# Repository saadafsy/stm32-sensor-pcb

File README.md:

# STM32F411 Sensor Telemetry Board — Firmware

Bare-metal C (no HAL, direct CMSIS) + FreeRTOS firmware for a custom **4-layer** STM32F411RET6
sensor telemetry board. A BME280 environmental sensor and a 128×64 **SSD1306 OLED** share one
400 kHz I²C bus, arbitrated by a FreeRTOS mutex. Sensor readings are framed with a CRC-16/CCITT
protocol and streamed at 921600 baud over a CP2102N USB-UART bridge to a Python visualizer.

## Architecture — four FreeRTOS tasks
- **sensor_task** — reads + Bosch-compensates the BME280 over I²C, pushes samples to a queue
- **telemetry_task** — builds the CRC-framed binary packet and sends it under a UART mutex
- **display_task** — renders pages to the SSD1306; a **PA0/EXTI0 button** cycles pages via an ISR notification
- **heartbeat_task** — blinks the PA5 LED and kicks the IWDG watchdog

Shared I²C access is protected by an `i2c_mutex`; an `i2c_bus_recovery()` routine frees a wedged bus.

## Hardware (locked spec)
- MCU: **STM32F411RET6, LQFP-64** (LCSC C94355)
- PCB: **4-layer** — `F.Cu` signal / `In1.Cu` ground plane / `In2.Cu` +3V3 plane / `B.Cu` signal, 1.6 mm FR4
- BME280 @ I²C **0x77** (SDO→+3V3) · SSD1306 @ I²C **0x3C** · CP2102N USB-UART
- Clock: 8 MHz HSE → PLL → 100 MHz

## Layout
```
Core/Inc/   headers (clock, gpio, uart, i2c, bme280, crc, protocol, ssd1306, iwdg, FreeRTOSConfig)
Core/Src/   sources (+ main.c with the four tasks and the EXTI button ISR)
tools/      visualize.py — host-side telemetry viewer
hardware/   KiCad project (schematic, PCB, project)
docs/img/   board renders
```

## Build
Import into **STM32CubeIDE** as a bare-metal + FreeRTOS project for the STM32F411RET6
(develop on a NUCLEO-F411RE, deploy on the custom PCB). Flash over SWD/ST-Link.

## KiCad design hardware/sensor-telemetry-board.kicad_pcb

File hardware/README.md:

# Hardware

Custom 4-layer PCB designed in KiCad 9 (stackup: F.Cu / inner GND / inner +3V3 / B.Cu).

- `sensor-telemetry-board.kicad_pro` - project
- `sensor-telemetry-board.kicad_sch` - schematic
- `sensor-telemetry-board.kicad_pcb` - 4-layer layout

## Key parts

| Ref | Part | Role |
|-----|------|------|
| U1 | STM32F411CEU6 | MCU (Cortex-M4F, 100 MHz) |
| U? | BME280 | temperature / humidity / pressure over I2C |
| U? | CP2102N | USB-C to UART bridge |
| U? | AMS1117-3.3 | 3.3 V LDO |
| U? | USBLC6-2 | USB data-line ESD protection |
| Y1 | 8 MHz crystal | HSE reference for the 100 MHz PLL |

## Status

Design complete and DFM-validated (POFV across all vias); Gerbers, BOM, and CPL
can be regenerated from this project for a JLCPCB PCBA order. The board is in shipping 
and will be brought up soon (see the top-level README for status).

To export fabrication files: open the project in KiCad and run the Fabrication
Toolkit plugin, or export Gerbers / drill / BOM / CPL manually from the PCB and
schematic editors.

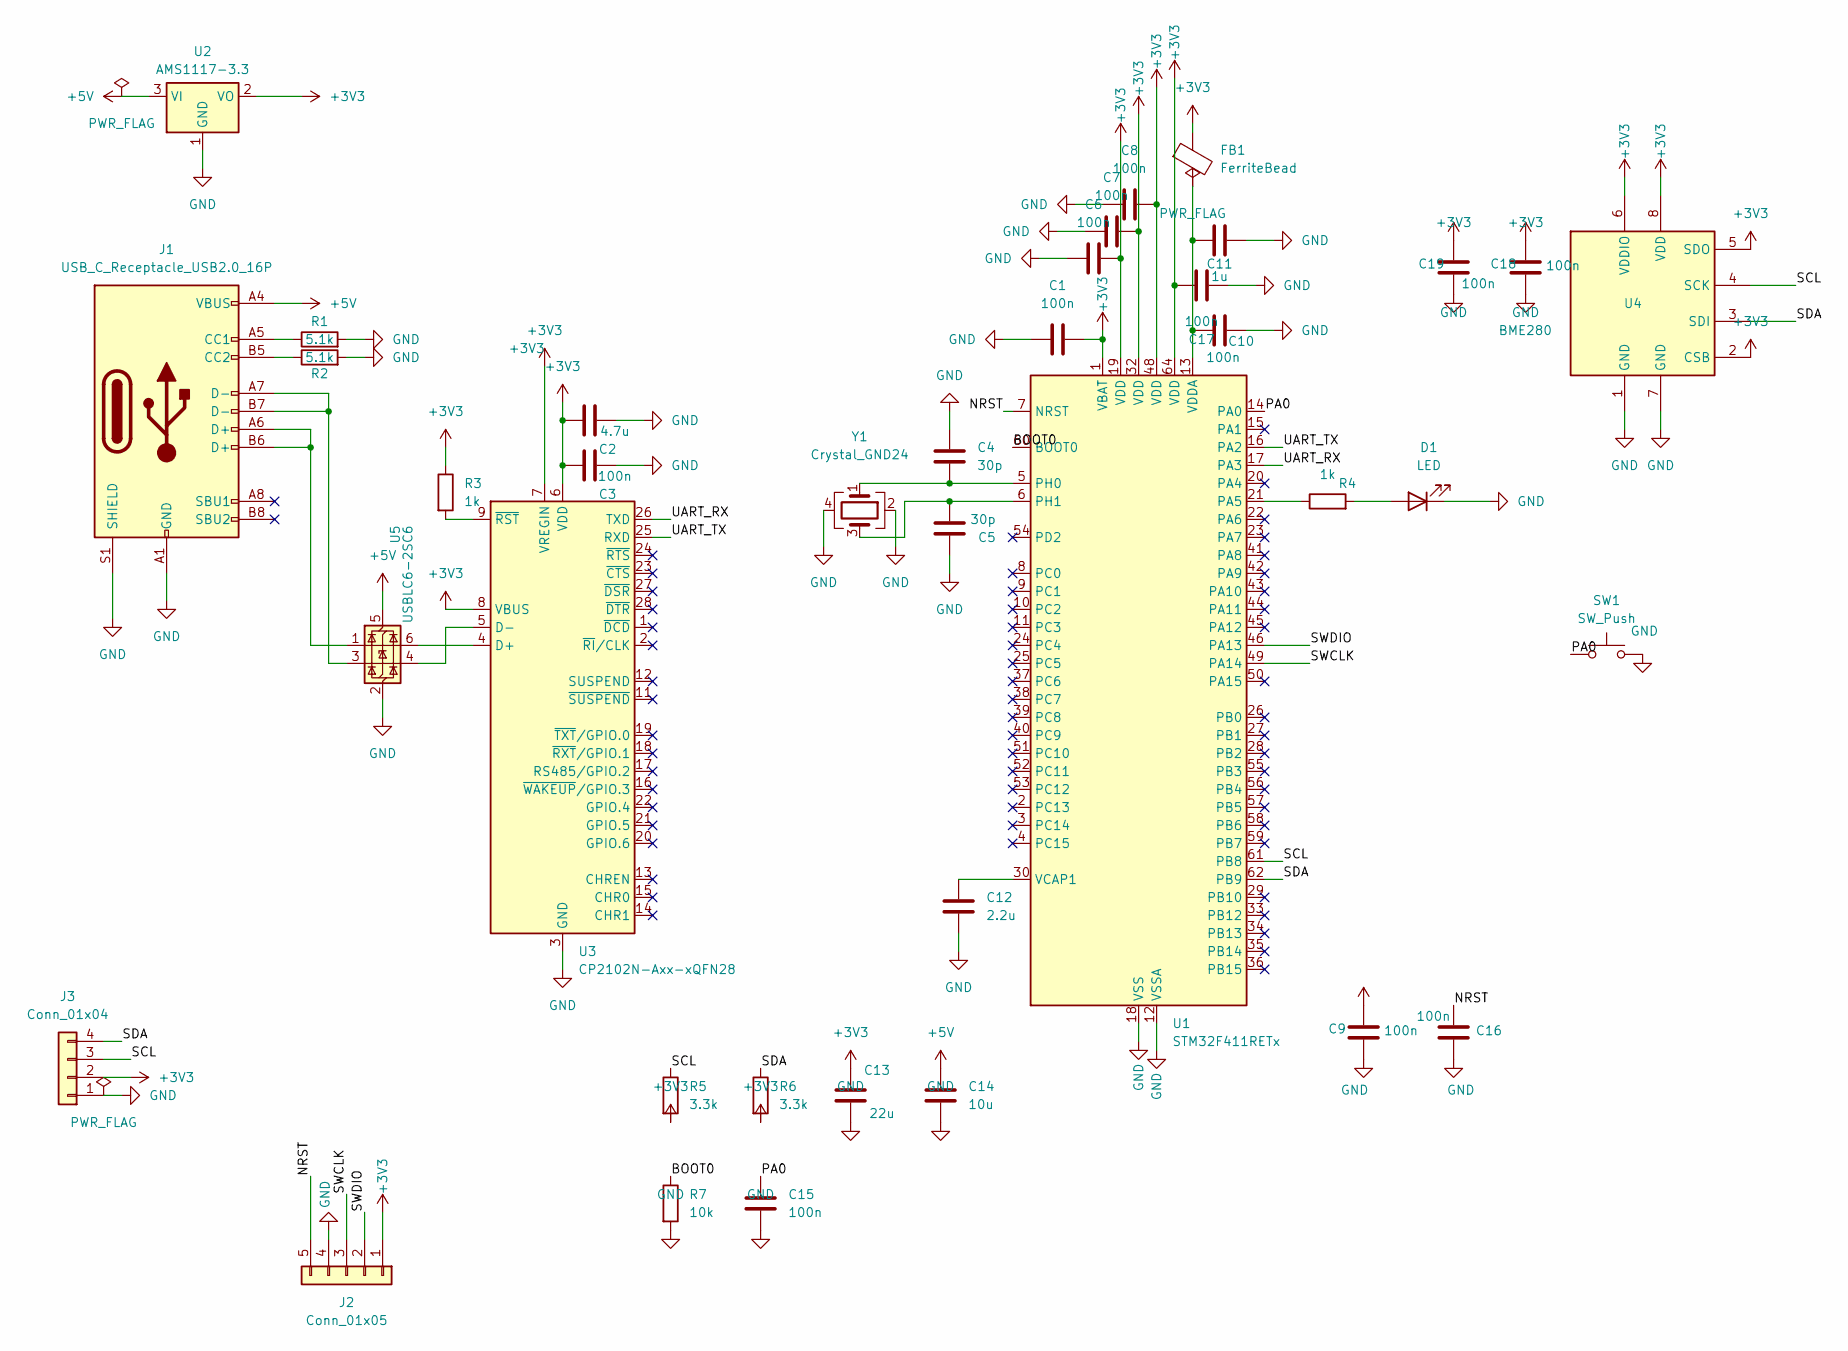
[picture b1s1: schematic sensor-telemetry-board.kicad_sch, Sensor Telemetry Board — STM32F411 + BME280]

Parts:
C1, C3, C6, C7, C8, C9, C10, C15, C16, C17, C18, C19: 100n; C_0402_1005Metric
C2: 4.7u; C_0603_1608Metric
C4, C5: 30p; C_0402_1005Metric
C11: 1u; C_0402_1005Metric
C12: 2.2u; C_0603_1608Metric
C13: 22u; C_0805_2012Metric
C14: 10u; C_0805_2012Metric
D1: LED; LED_0603_1608Metric
FB1: FerriteBead; L_0603_1608Metric
J1: USB_C_Receptacle_USB2.0_16P; USB_C_Receptacle_HRO_TYPE-C-31-M-12
J2: Conn_01x05; PinHeader_1x05_P2.54mm_Vertical
J3: Conn_01x04; PinHeader_1x04_P2.54mm_Vertical
R1, R2: 5.1k; R_0402_1005Metric
R3, R4: 1k; R_0402_1005Metric
R5, R6: 3.3k; R_0402_1005Metric
R7: 10k; R_0402_1005Metric
SW1: SW_Push; SW_SPST_PTS645Sx43SMTR92
U1: STM32F411RETx; LQFP-64_10x10mm_P0.5mm
U2: AMS1117-3.3; SOT-223-3_TabPin2
U3: CP2102N-Axx-xQFN28; QFN-28-1EP_5x5mm_P0.5mm_EP3.35x3.35mm
U4: BME280; Bosch_LGA-8_2.5x2.5mm_P0.65mm_ClockwisePinNumbering
U5: USBLC6-2SC6; SOT-23-6
Y1: Crystal_GND24; Crystal_SMD_3225-4Pin_3.2x2.5mm

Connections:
+3V3: C1.2, C2.2, C3.2, C6.2, C7.2, C8.2, C9.1, C13.1, C17.2, C18.1, C19.1, FB1.1, J2.1, J3.2, R3.1, R5.2, R6.2, U1.1 (VBAT), U1.19 (VDD), U1.32 (VDD), U1.48 (VDD), U1.64 (VDD), U2.2 (VO), U3.6 (VDD), U3.7 (VREGIN), U3.8 (VBUS), U4.2 (CSB), U4.5 (SDO), U4.6 (VDDIO), U4.8 (VDD)
+5V: C14.1, J1.A4 (VBUS), J1.A9 (VBUS), J1.B4 (VBUS), J1.B9 (VBUS), U2.3 (VI), U5.5 (VBUS)
/BOOT0: R7.1, U1.60 (BOOT0)
/NRST: C16.1, J2.5, U1.7 (NRST)
/PA0: C15.1, SW1.1, U1.14 (PA0)
/SCL: J3.3, R5.1, U1.61 (PB8), U4.4 (SCK)
/SDA: J3.4, R6.1, U1.62 (PB9), U4.3 (SDI)
/SWCLK: J2.3, U1.49 (PA14)
/SWDIO: J2.2, U1.46 (PA13)
/UART_RX: U1.17 (PA3), U3.26 (TXD)
/UART_TX: U1.16 (PA2), U3.25 (RXD)
GND: C1.1, C2.1, C3.1, C4.1, C5.1, C6.1, C7.1, C8.1, C9.2, C10.1, C11.1, C12.2, C13.2, C14.2, C15.2, C16.2, C17.1, C18.2, C19.2, D1.1 (K), J1.A1 (GND), J1.A12 (GND), J1.B1 (GND), J1.B12 (GND), J1.S1 (SHIELD), J2.4, J3.1, R1.2, R2.2, R7.2, SW1.2, U1.12 (VSSA), U1.18 (VSS), U1.31 (VSS), U1.47 (VSS), U1.63 (VSS), U2.1 (GND), U3.3 (GND), U3.29 (GND), U4.1 (GND), U4.7 (GND), U5.2 (GND), Y1.2, Y1.4
unnamed: D1.2 (A), R4.2
unnamed: J1.A5 (CC1), R1.1
unnamed: J1.B5 (CC2), R2.1
unnamed: J1.A6 (D+), J1.B6 (D+), U5.1 (I/O1)
unnamed: J1.A7 (D-), J1.B7 (D-), U5.3 (I/O2)
unnamed: R4.1, U1.21 (PA5)
unnamed: C4.2, U1.5 (PH0), Y1.1
unnamed: C5.2, U1.6 (PH1), Y1.3
unnamed: C12.1, U1.30 (VCAP1)
unnamed: C10.2, C11.2, FB1.2, U1.13 (VDDA)
unnamed: U3.4 (D+), U5.6 (I/O1)
unnamed: U3.5 (D-), U5.4 (I/O2)
unnamed: R3.2, U3.9 (~RST)

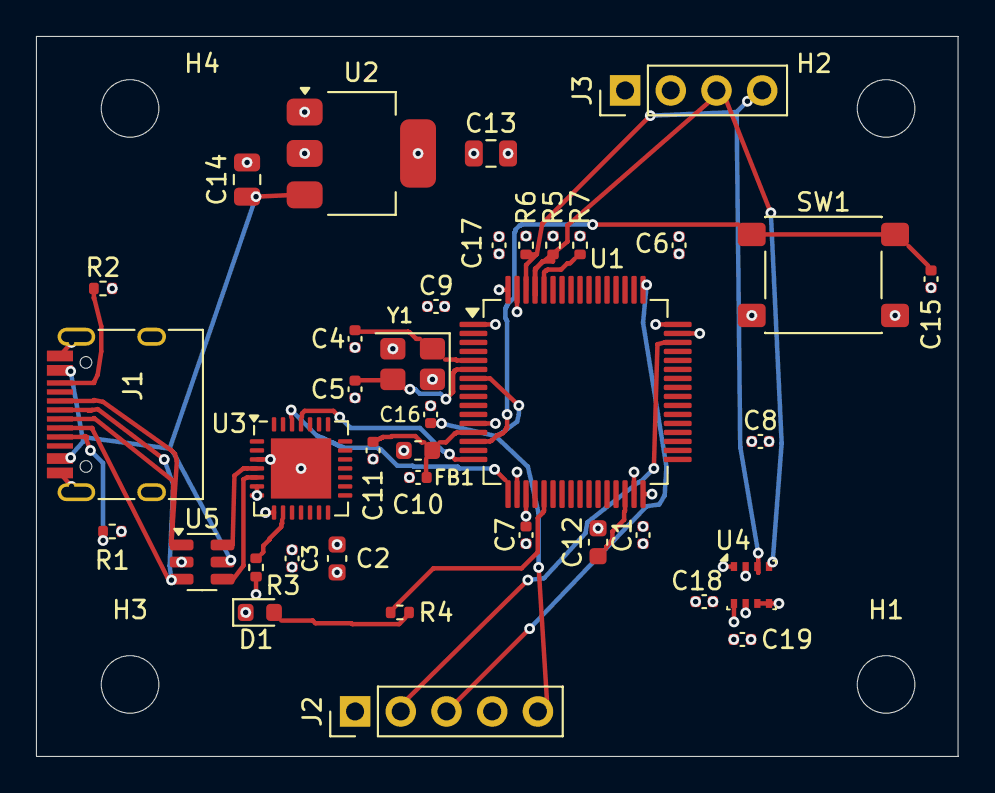
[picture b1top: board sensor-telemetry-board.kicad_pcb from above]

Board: 4 copper layers, 51.2 x 40.0 mm, 42 parts (0 on the bottom side), 25 nets.

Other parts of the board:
H1, H2, H3, H4: MountingHole_3.2mm_M3
